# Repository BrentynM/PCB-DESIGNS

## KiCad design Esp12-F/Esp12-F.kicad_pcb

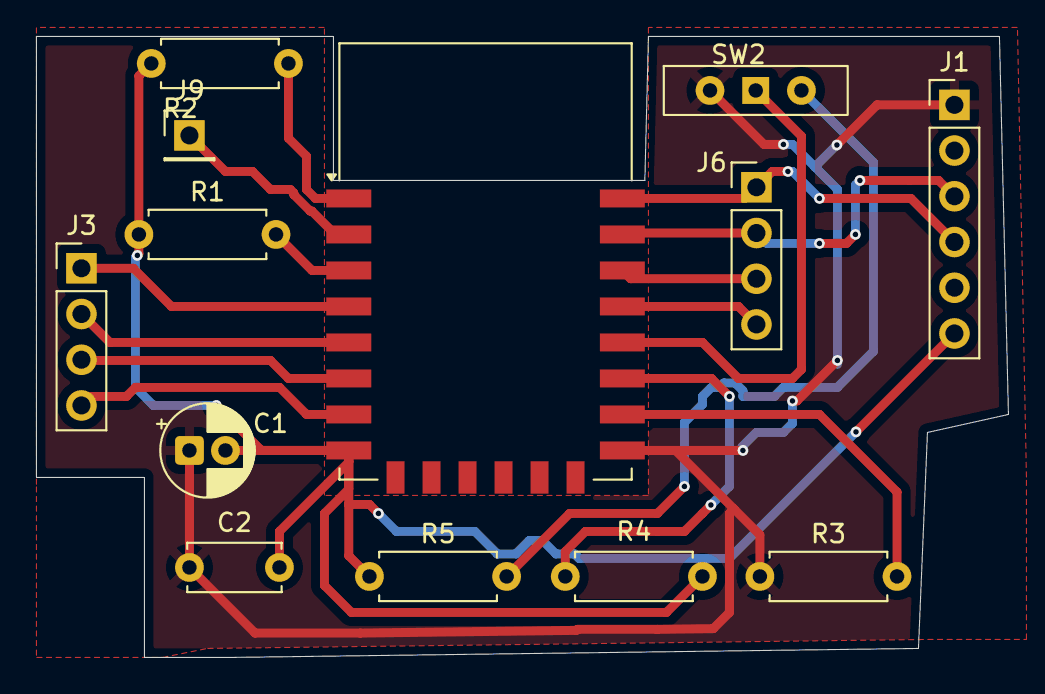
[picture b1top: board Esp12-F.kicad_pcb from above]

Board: 2 copper layers, 54.0 x 34.5 mm, 13 parts (0 on the bottom side), 17 nets.

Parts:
C1: 10uF; CP_Radial_D5.0mm_P2.00mm
C2: 100nF; C_Disc_D5.0mm_W2.5mm_P5.00mm
J1: Conn_01x06_Pin; PinHeader_1x06_P2.54mm_Vertical
J3, J6: Conn_01x04_Pin; PinHeader_1x04_P2.54mm_Vertical
J9: Conn_01x01_Pin; PinHeader_1x01_P2.54mm_Vertical
R1, R2, R3, R4, R5: 10k; R_Axial_DIN0207_L6.3mm_D2.5mm_P7.62mm_Horizontal
SW2: SW_SPDT; SW_Slide-03_Wuerth-WS-SLTV_10x2.5x6.4_P2.54mm
U1: ESP-12F; ESP-12E

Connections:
3.3V: C1.2, C2.2, J1.6, R1.1, R2.1, R4.1, R5.1, U1.8 (VCC)
GND: C1.1, C2.1, J1.1, R3.1, SW2.2 (B), U1.15 (GND)
unnamed: J1.3, J6.2, U1.21 (GPIO3/RXD)
unnamed: J1.4, J6.1, U1.22 (GPIO1/TXD)
unnamed: J3.1, U1.4 (GPIO16)
unnamed: J3.2, U1.5 (GPIO14)
unnamed: J3.3, U1.6 (GPIO12)
unnamed: J3.4, U1.7 (GPIO13)
unnamed: J6.3, U1.20 (GPIO5)
unnamed: J6.4, U1.19 (GPIO4)
unnamed: J9.1, U1.2 (ADC)
unnamed: SW2.1 (A), U1.18 (GPIO0)
unnamed: R5.2, SW2.3 (C)
unnamed: R1.2, U1.3 (EN)
unnamed: R4.2, U1.17 (GPIO2)
unnamed: R3.2, U1.16 (GPIO15)
unnamed: R2.2, U1.1 (~RST)

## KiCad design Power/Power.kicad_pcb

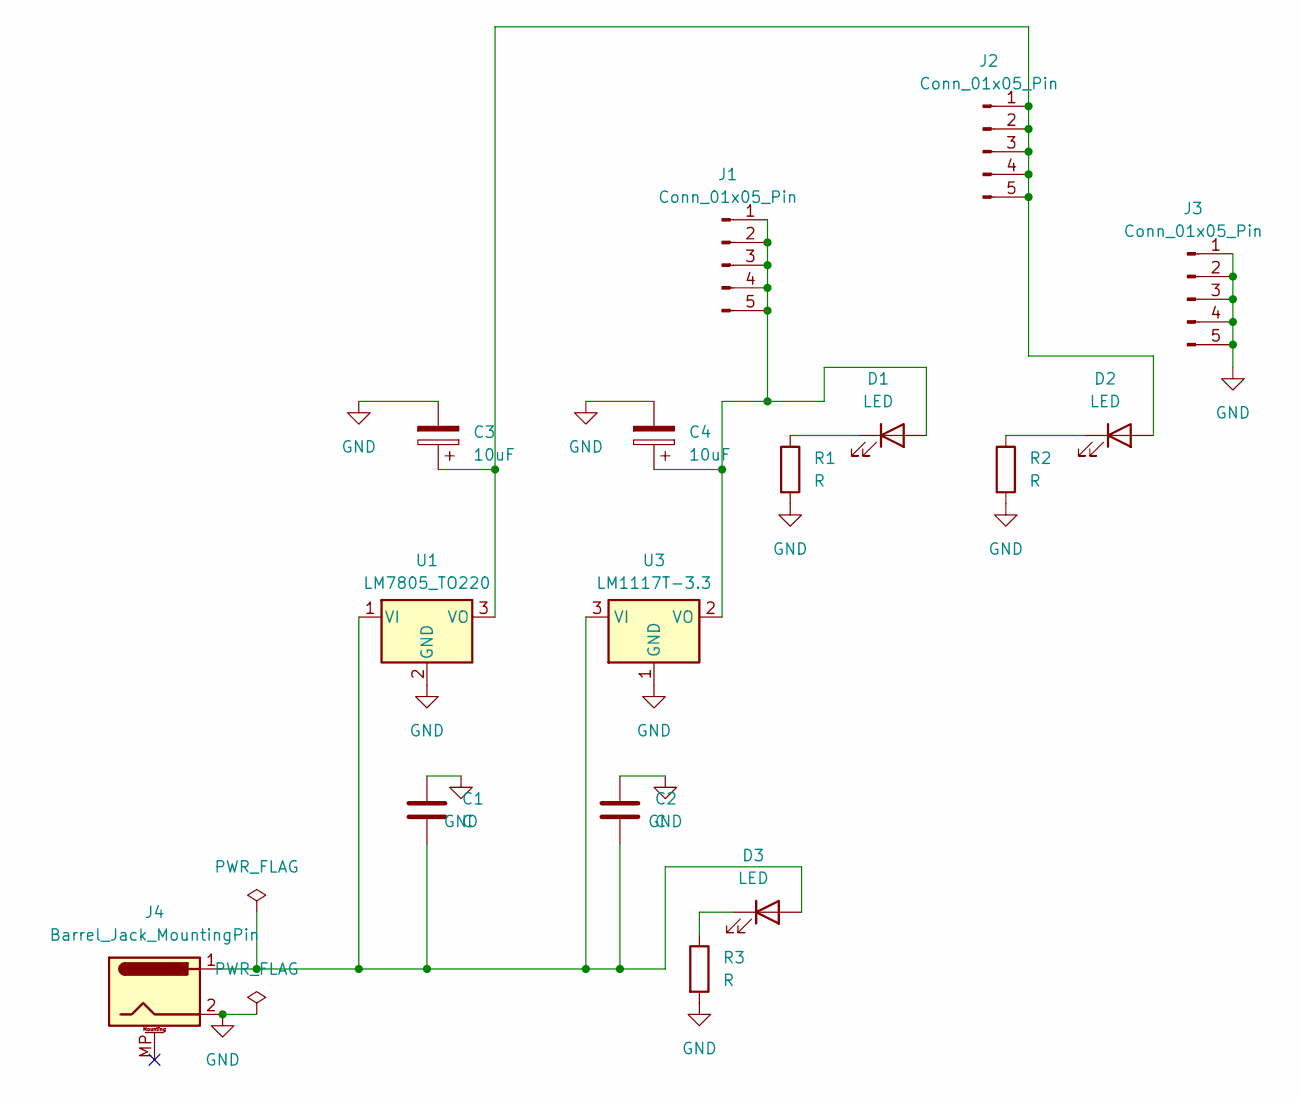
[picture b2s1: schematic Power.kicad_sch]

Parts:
C1, C2: C; C_Disc_D5.0mm_W2.5mm_P2.50mm
C3, C4: 10uF; CP_Radial_D6.3mm_P2.50mm
D1, D2, D3: LED; LED_D5.0mm
J1, J2, J3: Conn_01x05_Pin; PinHeader_1x05_P2.54mm_Vertical
J4: Barrel_Jack_MountingPin; BarrelJack_Horizontal
R1, R2, R3: R; R_Axial_DIN0207_L6.3mm_D2.5mm_P7.62mm_Horizontal
U1: LM7805_TO220; TO-220-3_Vertical
U3: LM1117T-3.3; TO-220-3_Vertical

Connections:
GND: C1.1, C2.1, C3.2, C4.2, J3.1, J3.2, J3.3, J3.4, J3.5, J4.2, R1.2, R2.2, R3.2, U1.2 (GND), U3.1 (GND)
unnamed: C4.1, D1.2 (A), J1.1, J1.2, J1.3, J1.4, J1.5, U3.2 (VO)
unnamed: D1.1 (K), R1.1
unnamed: C3.1, D2.2 (A), J2.1, J2.2, J2.3, J2.4, J2.5, U1.3 (VO)
unnamed: D2.1 (K), R2.1
unnamed: C1.2, C2.2, D3.2 (A), J4.1, U1.1 (VI), U3.3 (VI)
unnamed: D3.1 (K), R3.1

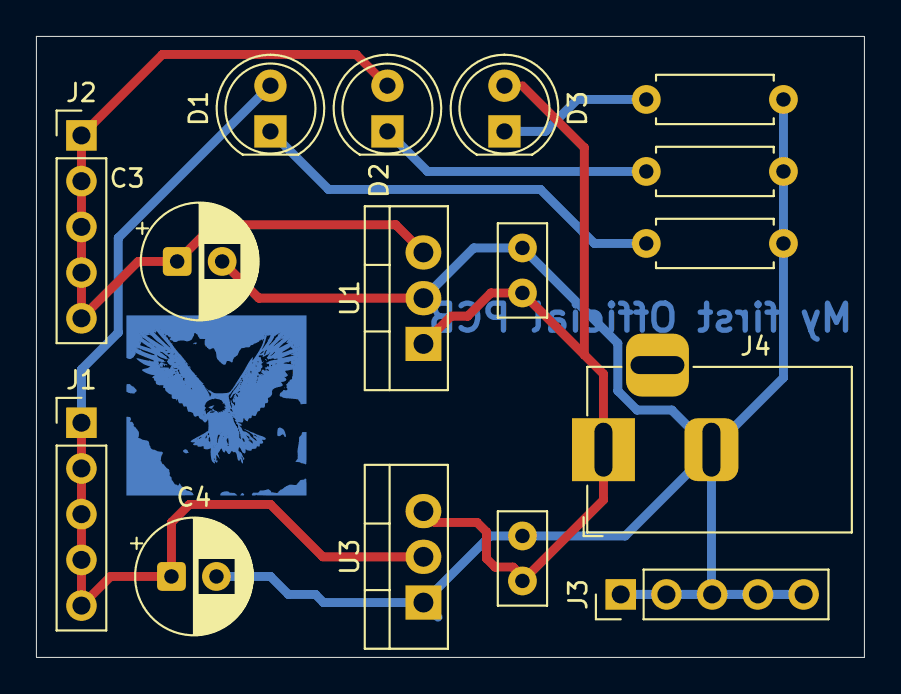
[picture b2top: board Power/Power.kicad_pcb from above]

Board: 2 copper layers, 46.0 x 34.5 mm, 16 parts (0 on the bottom side), 7 nets.

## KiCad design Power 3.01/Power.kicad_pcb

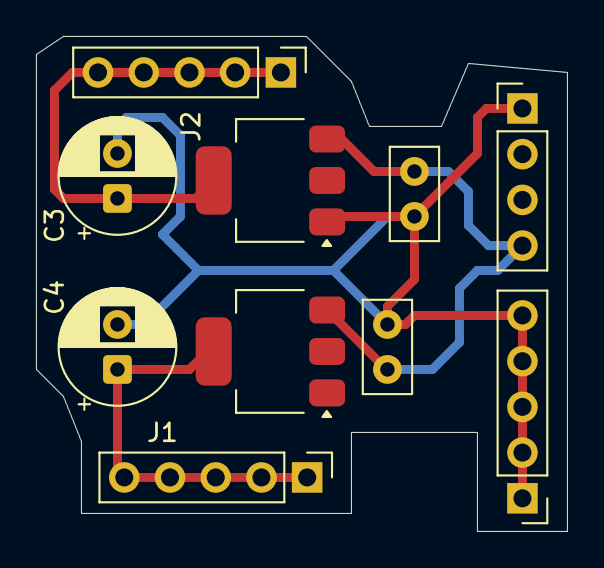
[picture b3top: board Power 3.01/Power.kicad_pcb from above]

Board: 2 copper layers, 29.5 x 27.5 mm, 10 parts (0 on the bottom side), 4 nets.

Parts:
3.3 VR: AMS1117-3.3; SOT-223-3_TabPin2
5.0 VR: AMS1117-5.0; SOT-223-3_TabPin2
C1, C2: C; C_Disc_D5.0mm_W2.5mm_P2.50mm
C3, C4: 10uF; CP_Radial_D6.3mm_P2.50mm
GND: Conn_01x05_Pin; PinHeader_1x05_P2.54mm_Vertical
J1, J2: Conn_01x05_Pin; PinHeader_1x05_P2.54mm_Vertical
USB-C: Conn_01x04_Pin; PinHeader_1x04_P2.54mm_Vertical

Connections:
GND: 3.3 VR.1 (GND), 5.0 VR.1 (GND), C1.1, C2.1, C3.2, C4.2, GND.1, GND.2, GND.3, GND.4, GND.5, USB-C.1
unnamed: 3.3 VR.2 (VO), C4.1, J1.1, J1.2, J1.3, J1.4, J1.5
unnamed: 5.0 VR.2 (VO), C3.1, J2.1, J2.2, J2.3, J2.4, J2.5
unnamed: 3.3 VR.3 (VI), 5.0 VR.3 (VI), C1.2, C2.2, USB-C.4
